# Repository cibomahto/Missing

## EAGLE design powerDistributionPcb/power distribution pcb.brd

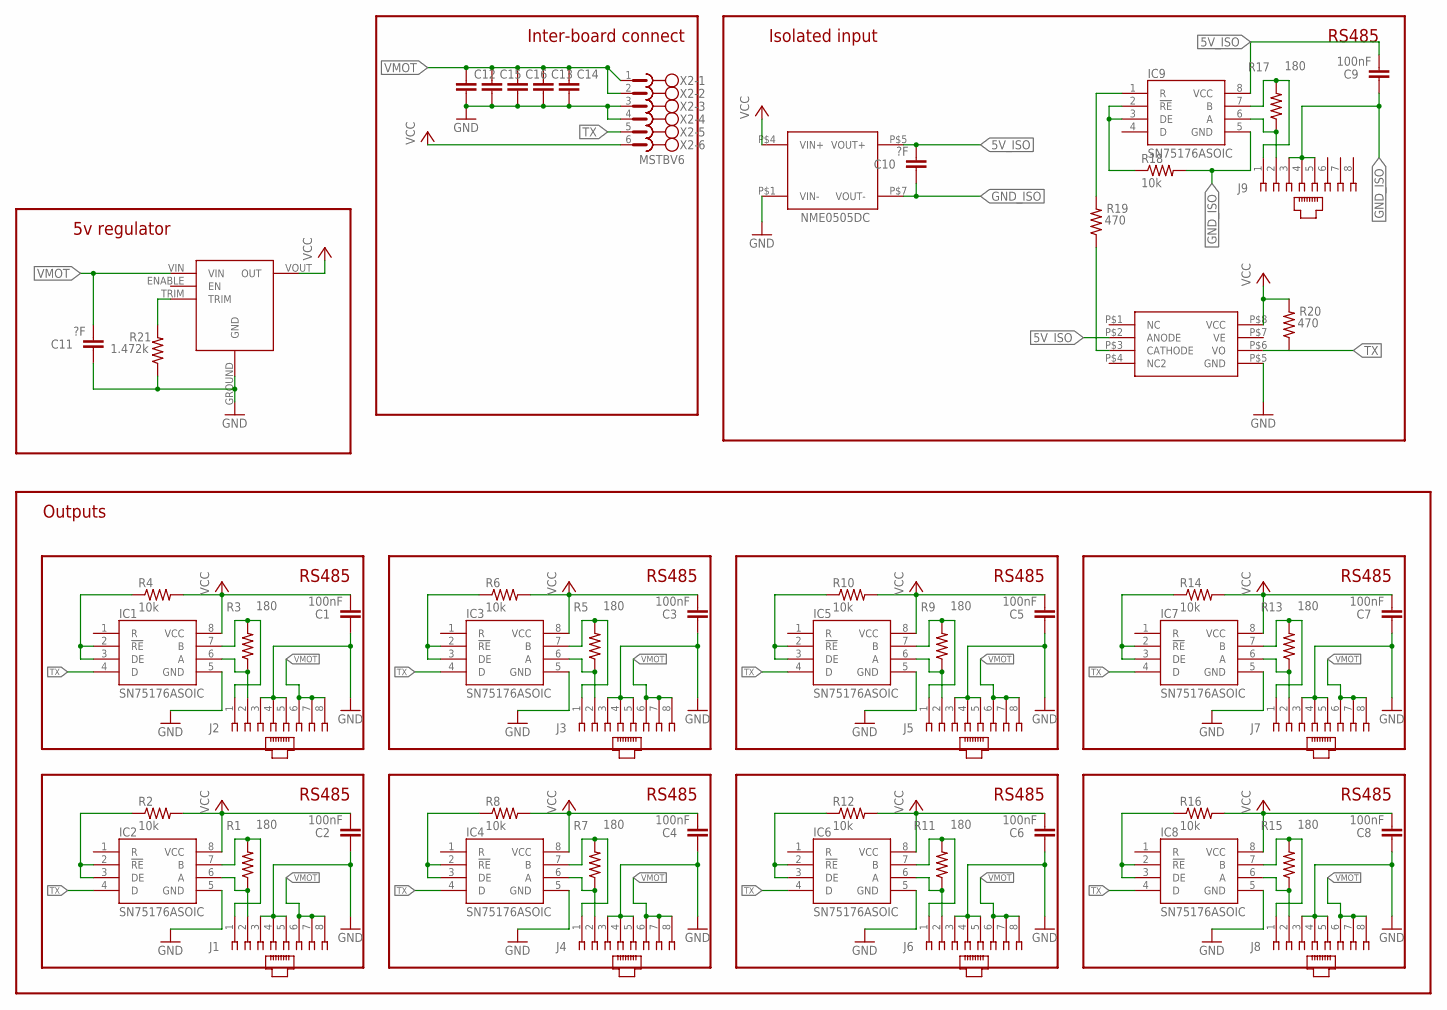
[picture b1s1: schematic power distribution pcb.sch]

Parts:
C1, C2, C3, C4, C5, C6, C7, C8, C9: 100nF; 0805
C10, C11: ?F; 0805
C12, C13, C14, C15, C16: CAP1210; 1210
IC1, IC2, IC3, IC4, IC5, IC6, IC7, IC8, IC9: SN75176ASOIC; SO08
J1, J2, J3, J4, J5, J6, J7, J8, J9: 520426-4
R1, R3, R5, R7, R9, R11, R13, R15, R17: 180; 0805
R2, R4, R6, R8, R10, R12, R14, R16, R18: 10k; 0805
R19, R20: 470; 0805
R21: 1.472k; 0805
U$1: NME0505DC
U$2: OKI-T/3-W40N-C
U$3: 6N137; 8_SOIC
X2: MSTBV6

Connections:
5V_ISO: C9.2, C10.2, IC9.8 (VCC), U$1.P$5 (VOUT+), U$3.P$2 (ANODE)
D1: IC1.2 (!RE), IC1.3 (DE), R4.1
D2: IC2.2 (!RE), IC2.3 (DE), R2.1
D3: IC3.2 (!RE), IC3.3 (DE), R6.1
D4: IC4.2 (!RE), IC4.3 (DE), R8.1
D5: IC5.2 (!RE), IC5.3 (DE), R10.1
D6: IC6.2 (!RE), IC6.3 (DE), R12.1
D7: IC7.2 (!RE), IC7.3 (DE), R14.1
D8: IC8.2 (!RE), IC8.3 (DE), R16.1
D9: IC9.2 (!RE), IC9.3 (DE), R18.1
GND: C1.1, C2.1, C3.1, C4.1, C5.1, C6.1, C7.1, C8.1, C11.1, C12.2, C13.2, C14.2, C15.2, C16.2, IC1.5 (GND), IC2.5 (GND), IC3.5 (GND), IC4.5 (GND), IC5.5 (GND), IC6.5 (GND), IC7.5 (GND), IC8.5 (GND), J1.3, J1.4, J1.5, J2.3, J2.4, J2.5, J3.3, J3.4, J3.5, J4.3, J4.4, J4.5, J5.3, J5.4, J5.5, J6.3, J6.4, J6.5, J7.3, J7.4, J7.5, J8.3, J8.4, J8.5, R21.1, U$1.P$1 (VIN-), U$2.GROUND (GND), U$3.P$5 (GND), X2.3, X2.4
GND_ISO: C9.1, C10.1, IC9.5 (GND), J9.3, J9.4, J9.5, R18.2, U$1.P$7 (VOUT-)
unnamed: R19.1, U$3.P$3 (CATHODE)
unnamed: IC9.1 (R), R19.2
unnamed: R21.2, U$2.TRIM
RS485A1: IC1.6 (A), J2.2, R3.1
RS485A2: IC2.6 (A), J1.2, R1.1
RS485A3: IC3.6 (A), J3.2, R5.1
RS485A4: IC4.6 (A), J4.2, R7.1
RS485A5: IC5.6 (A), J5.2, R9.1
RS485A6: IC6.6 (A), J6.2, R11.1
RS485A7: IC7.6 (A), J7.2, R13.1
RS485A8: IC8.6 (A), J8.2, R15.1
RS485A9: IC9.6 (A), J9.2, R17.1
RS485B1: IC1.7 (B), J2.1, R3.2
RS485B2: IC2.7 (B), J1.1, R1.2
RS485B3: IC3.7 (B), J3.1, R5.2
RS485B4: IC4.7 (B), J4.1, R7.2
RS485B5: IC5.7 (B), J5.1, R9.2
RS485B6: IC6.7 (B), J6.1, R11.2
RS485B7: IC7.7 (B), J7.1, R13.2
RS485B8: IC8.7 (B), J8.1, R15.2
RS485B9: IC9.7 (B), J9.1, R17.2
TX: IC1.4 (D), IC2.4 (D), IC3.4 (D), IC4.4 (D), IC5.4 (D), IC6.4 (D), IC7.4 (D), IC8.4 (D), R20.1, U$3.P$6 (VO), X2.5
VCC: C1.2, C2.2, C3.2, C4.2, C5.2, C6.2, C7.2, C8.2, IC1.8 (VCC), IC2.8 (VCC), IC3.8 (VCC), IC4.8 (VCC), IC5.8 (VCC), IC6.8 (VCC), IC7.8 (VCC), IC8.8 (VCC), R2.2, R4.2, R6.2, R8.2, R10.2, R12.2, R14.2, R16.2, R20.2, U$1.P$4 (VIN+), U$2.VOUT (OUT), U$3.P$8 (VCC), X2.6
VMOT: C11.2, C12.1, C13.1, C14.1, C15.1, C16.1, J1.6, J1.7, J1.8, J2.6, J2.7, J2.8, J3.6, J3.7, J3.8, J4.6, J4.7, J4.8, J5.6, J5.7, J5.8, J6.6, J6.7, J6.8, J7.6, J7.7, J7.8, J8.6, J8.7, J8.8, U$2.VIN, X2.1, X2.2

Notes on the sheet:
RS485
Outputs
Isolated input
Inter-board connect
5v regulator

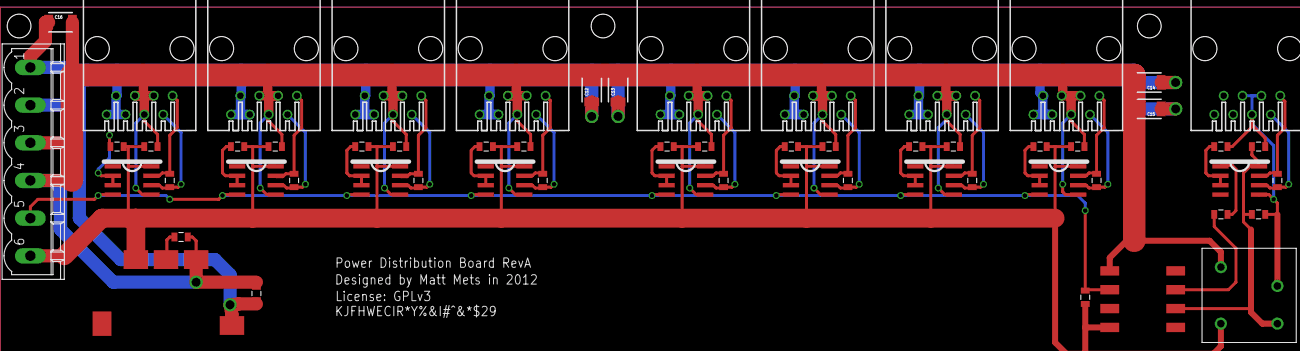
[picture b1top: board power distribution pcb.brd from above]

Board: 2 copper layers, 59 parts (0 on the bottom side), 36 nets.

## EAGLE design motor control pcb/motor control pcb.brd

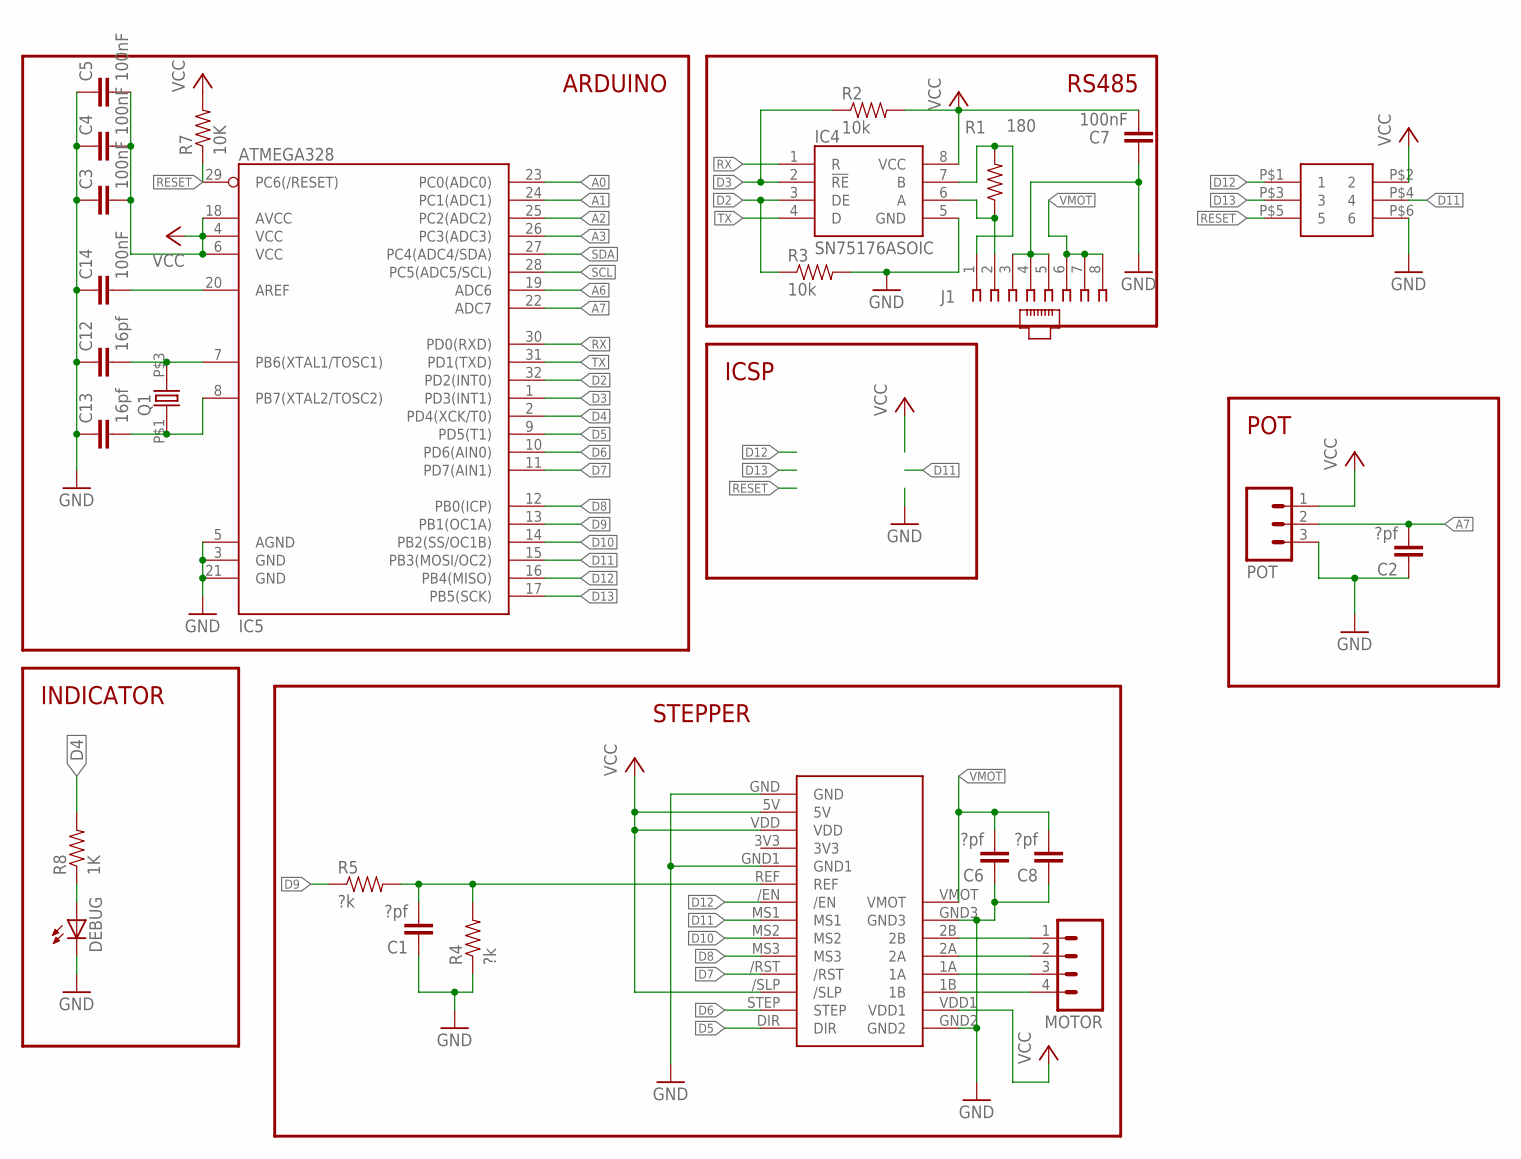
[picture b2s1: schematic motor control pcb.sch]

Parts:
C1, C2, C6: ?pf; 0805
C3, C4, C5, C7, C14: 100nF; 0805
C8: ?pf; 1210
C12, C13: 16pf; 0805
DEBUG: LED0805; LED-0805
IC4: SN75176ASOIC; SO08
IC5: ATMEGA328; TQFP32-08
J1: 520426-4
MOTOR: M04PTH; 1X04
POT: M03PTH; 1X03
Q1: GLOWBOARD_ABMM2; GLOWBOARD_ABMM2_CRYSTAL
R1: 180; 0805
R2, R3: 10k; 0805
R4, R5: ?k; 0805
R7: 10K; 0805
R8: 1K; 0805
U$1: POLOLU_DRIVER
U$2: 2X3HEADER

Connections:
A0: IC5.23 (PC0(ADC0))
A1: IC5.24 (PC1(ADC1))
A2: IC5.25 (PC2(ADC2))
A3: IC5.26 (PC3(ADC3))
A6: IC5.19 (ADC6)
A7: C2.2, IC5.22 (ADC7), POT.2
D2: IC4.3 (DE), IC5.32 (PD2(INT0)), R3.1
D3: IC4.2 (!RE), IC5.1 (PD3(INT1)), R2.1
D4: IC5.2 (PD4(XCK/T0)), R8.2
D5: IC5.9 (PD5(T1)), U$1.DIR
D6: IC5.10 (PD6(AIN0)), U$1.STEP
D7: IC5.11 (PD7(AIN1)), U$1./RST
D8: IC5.12 (PB0(ICP)), U$1.MS3
D9: IC5.13 (PB1(OC1A)), R5.1
D10: IC5.14 (PB2(SS/OC1B)), U$1.MS2
D11: IC5.15 (PB3(MOSI/OC2)), U$1.MS1, U$2.P$4 (4)
D12: IC5.16 (PB4(MISO)), U$1./EN, U$2.P$1 (1)
D13: IC5.17 (PB5(SCK)), U$2.P$3 (3)
GND: C1.1, C2.1, C3.1, C4.1, C5.1, C6.1, C7.1, C8.1, C12.1, C13.1, C14.1, DEBUG.C, IC4.5 (GND), IC5.3 (GND), IC5.5 (AGND), IC5.21 (GND), J1.3, J1.4, J1.5, POT.3, R3.2, R4.1, U$1.GND, U$1.GND1, U$1.GND2, U$1.GND3, U$2.P$6 (6)
unnamed: MOTOR.1, U$1.2B
unnamed: MOTOR.2, U$1.2A
unnamed: MOTOR.3, U$1.1A
unnamed: MOTOR.4, U$1.1B
unnamed: C13.2, IC5.8 (PB7(XTAL2/TOSC2)), Q1.P$1 (1)
unnamed: DEBUG.A, R8.1
unnamed: C1.2, R4.2, R5.2, U$1.REF
unnamed: C14.2, IC5.20 (AREF)
unnamed: C12.2, IC5.7 (PB6(XTAL1/TOSC1)), Q1.P$3 (2)
RESET: IC5.29 (PC6(/RESET)), R7.1, U$2.P$5 (5)
RS485A: IC4.6 (A), J1.2, R1.1
RS485B: IC4.7 (B), J1.1, R1.2
RX: IC4.1 (R), IC5.30 (PD0(RXD))
SCL: IC5.28 (PC5(ADC5/SCL))
SDA: IC5.27 (PC4(ADC4/SDA))
TX: IC4.4 (D), IC5.31 (PD1(TXD))
VCC: C3.2, C4.2, C5.2, C7.2, IC4.8 (VCC), IC5.4 (VCC), IC5.6 (VCC), IC5.18 (AVCC), POT.1, R2.2, R7.2, U$1.5V, U$1./SLP, U$1.VDD, U$1.VDD1, U$2.P$2 (2)
VMOT: C6.2, C8.2, J1.6, J1.7, J1.8, U$1.VMOT

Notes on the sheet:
RS485
ICSP
ARDUINO
INDICATOR
STEPPER
POT

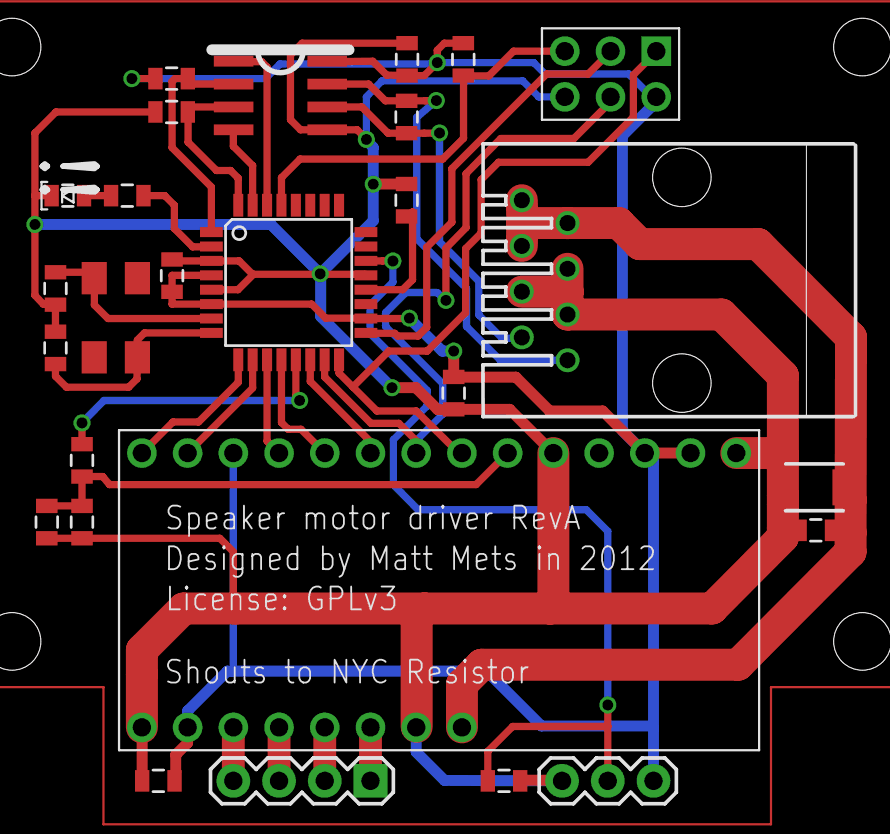
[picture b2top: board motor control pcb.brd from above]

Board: 2 copper layers, 27 parts (0 on the bottom side), 30 nets.

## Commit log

2012-10-02 Initial hardware design.
2012-10-03 Add lasercut files for 1/4 inch acryllic.
2012-10-04 Add protoypes for motor mount, shaft coupler.
2012-10-09 Add test program for stepper control.
2012-10-09 Lasercut plan for the stepper mount
2012-10-10 first pass at a servo loop. for demonstration only.
2012-10-10 Add Rhino model of speaker mount; still a wip
2012-10-11 Bugfix: enable the direction output...
2012-10-11 Add l-bracket mechanicals
2012-10-11 Work better and stuff.
2012-10-11 Switch to a different pot, add space for PCB
2012-10-11 Add quickie Processing example.
2012-10-12 Pull in MB extruder controller, as base for motor control pcb
2012-10-12 Motor control PCB
2012-10-13 Update for Rev A, sent for quotes.
2012-10-14 added play3 model and triangle mount
2012-10-14 wip on wiring
2012-10-15 Make the motor control more fancy.
2012-10-15 updated with total power
2012-10-15 Add revised triangle mount. Tested using 1/8" acrylic, and submitted for quotes.
2012-10-15 Bump motor plate to revA, changed gear size to match new steppers.
2012-10-16 Rev 0 of the motor control pcb; update for smaller traces.
2012-10-16 Add PCB libraries
2012-10-16 Clean up the motion control system; next is to address rapid direction change.
2012-10-16 Make board outline 2"x2"; need to center or make smaller.
2012-10-17 added some physical design specifications
2012-10-17 Update board again.
2012-10-17 Rearrange things.
2012-10-18 Board layout finished, need verification
2012-10-18 Finish laying out and verifying board. Bugfix: don't pull /sleep low.
2012-10-19 Motor control board Rev A, final.
2012-10-19 Motor plate Rev B (includes PCB mount)
2012-10-19 Get rid of unused hardware revs.
2012-10-19 Somewhat better!
2012-10-20 initial movement simulation for single speaker
2012-10-21 abstracted Speaker to class
2012-10-21 complete movement simulation
2012-10-21 added stepper simulation that should help a lot with debugging acceleration logic
2012-10-21 minor q to remember
2012-10-22 added better stepper code to simulation that deals with acceleration/deceleration nicely
2012-10-22 tried to fix name
2012-10-22 new stepper patterns
2012-10-22 all updated code for arduino and pde
2012-10-26 initial tracker just doing background calibration
2012-10-26 next step is getting the cloud aligned a la ofxVirtualKinect
2012-10-26 Add power distribution pcb.
2012-10-30 added basic presence detection image
2012-10-31 Update firmware for actual PCB.
2012-11-01 more controls for point cloud, some essential cv remains and some practical data massaging as well
2012-11-02 Update lasercut versions.
2012-11-02 Firmware bump.
2012-11-02 Add design files for power distribution board
2012-11-04 Firmware bump
2012-11-04 Add gerbers for the PCBs
2012-11-04 Add solder stencil design for the motor control board
2012-11-04 Iterate on the motor plate a bit more (TODO: gear spacing still incorrect)
2012-11-09 added initial app for visualizing entire setup in realtime
2012-11-09 position data and play3 3d model
2012-11-10 working on the smooth movement behavior
2012-11-10 xcode 4, driverinterface
2012-11-11 better speaker movement, crc, debug angles, automated interaction
2012-11-11 minor refactoring, simplifying todo
2012-11-11 added multiple debug views
2012-11-11 added midi output
2012-11-11 updated ofxMidi
2012-11-11 added bitmap font
2012-11-11 midi fixes
2012-11-11 added osc support
2012-11-11 added rotation
2012-11-11 updated project file
2012-11-11 Add processing implementation of the protocol
2012-11-11 added dual kinect example
2012-11-12 working on tracking code, added basic tracker
2012-11-12 trying to figure out why contours are no good, but it's just the way opencv works
2012-11-12 understand contours now, exporting data over osc
2012-11-12 Bump firmware, processing programming environment
2012-11-12 better valid pixel handling
2012-11-12 filtering kinect data
2012-11-12 refactoring
2012-11-13 moved KinectFilter to MissingTracker
2012-11-13 reorganizing to clarify move to more kinects
2012-11-13 moved all kinect specific code to KinectTracker
2012-11-13 dual kinects
2012-11-13 Update speaker motor controller
2012-11-13 Rename motor controller
2012-11-13 Minor debugger bump
2012-11-14 much better tracking, fixed bug with stretchy mesh
2012-11-14 added iir to presence
2012-11-14 versioning settings
2012-11-14 note changes
2012-11-15 added export and center
2012-11-15 refactoring to simplify controlp5 usage
2012-11-15 save calibration data
2012-11-15 calibration sliders fixed to ends
2012-11-15 added calibration data
2012-11-15 updated port, settings, orientation
2012-11-15 usb port should have been merged...
2012-11-15 made data safe, fixed some weird angular representation
2012-11-15 updated for new protocol
2012-11-15 starting to add the control panel
2012-11-15 Firmware bump, video version.
2012-11-15 Remove outdated processing example
2012-11-15 added more controls
2012-11-15 renamed before combining
2012-11-15 Move shit.
2012-11-15 Add production files for lasercut hardware
2012-11-15 Add final solder stencils
2012-11-15 Rename more stuff.
2012-11-15 Rename all the stuff.
2012-11-15 renaming before combining
2012-11-15 forgot to remove some things
2012-11-15 restore speakerMotorDebugger changes.
2012-11-15 combined missing app
2012-11-15 updated debugger, working towards final fixes to main app
2012-11-16 updated calibration
2012-11-16 better calibration
2012-11-16 added midi disable
2012-11-16 more calibration timing updates
2012-11-16 better calibration routine, more sound control
2012-11-16 added Rebuild script, changed schemes
2012-11-19 Add power distribution box plans, courtesy Max
2012-11-19 Remove duplicate solder stencil file.
2012-12-04 Add license info for PCBs and firmware.
2012-12-09 updated calibration with reduced min on speaker 0

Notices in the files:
motor control pcb/motor control pcb.brd:
License: GPLv3
